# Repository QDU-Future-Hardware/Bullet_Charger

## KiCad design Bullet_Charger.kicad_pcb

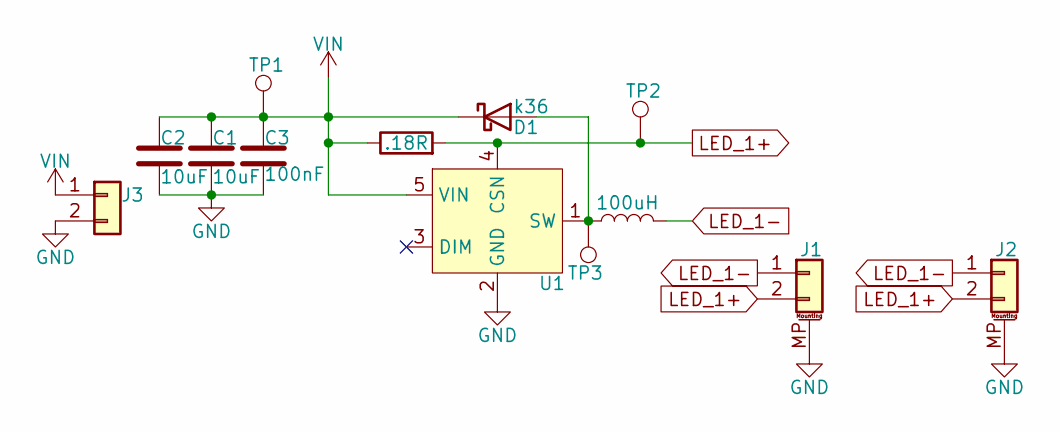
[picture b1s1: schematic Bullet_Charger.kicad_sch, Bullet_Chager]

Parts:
C1, C2: 10uF; C_1206_3216Metric
C3: 100nF; C_0603_1608Metric
D1: k36; D_SOD-123F
J1, J2: Conn_01x02_MountingPin; JST_GH_SM02B-GHS-TB_1x02-1MP_P1.25mm_Horizontal
J3: Conn_01x02; 无标题
L1: 100uH; L_Changjiang_FNR5040S
R1: .18R; R_1206_3216Metric
TP1, TP2, TP3: TestPoint; TestPoint_Pad_D1.0mm
U1: SOT-89-5

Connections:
GND: C1.2, C2.2, C3.2, J1.MP (MountPin), J2.MP (MountPin), J3.2, U1.2 (GND)
LED_1+: J1.2, J2.2, R1.2, TP2.1 (1_1), U1.4 (CSN)
LED_1-: J1.1, J2.1, L1.2
unnamed: D1.2 (A), L1.1, TP3.1 (1_1), U1.1 (SW)
VIN: C1.1, C2.1, C3.1, D1.1 (K), J3.1, R1.1, TP1.1 (1_1), U1.5 (VIN)

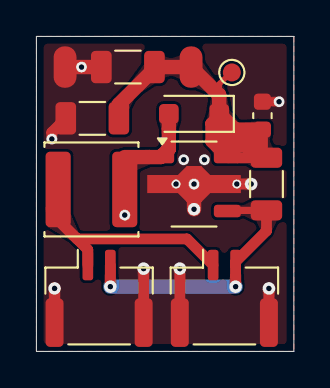
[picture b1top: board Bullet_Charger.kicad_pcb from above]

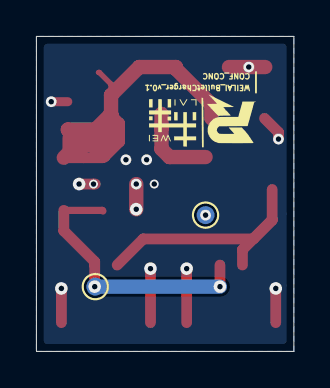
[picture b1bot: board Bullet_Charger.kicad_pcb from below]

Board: 2 copper layers, 14.3 x 17.5 mm, 13 parts (2 on the bottom side), 5 nets.

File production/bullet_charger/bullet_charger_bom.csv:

Designator,Footprint,Quantity,Value,LCSC Part #
"C1, C2",1206,2,10uF,
C3,0603,1,100nF,
D1,D_SOD-123F,1,k36,
"J1, J2",JST_GH_SM02B-GHS-TB_1x02-1MP_P1.25mm_Horizontal,2,Conn_01x02_MountingPin,
J3,无标题,1,Conn_01x02,
L1,L_Changjiang_FNR5040S,1,100uH,
R1,1206,1,.18R,
"TP1, TP2, TP3",TestPoint_Pad_D1.0mm,3,TestPoint,
U1,SOT-89-5,1,~,
